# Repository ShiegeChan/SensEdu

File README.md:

<p align="center"><b>Ultrasonic Development Shield for Arduino GIGA R1</b><br>
Designed for education - easy entry into ultrasonic sensing and research</p>

<p align="center">

</p>

<b>
<p align="center">
	<a href="https://github.com/ShiegeChan/SensEdu/releases" target="_blank">Download</a> ·
	<a href="https://sensedu-shield.com/getting-started/" target="_blank">Getting Started</a> ·
	<a href="https://sensedu-shield.com/projects/" target="_blank">Example Projects</a> ·
	<a href="https://sensedu-shield.com" target="_blank">Documentation</a> ·
	<a href="https://sensedu-shield.com/contributing/" target="_blank">Contribution</a>
</p>
</b>

## Features

* **Custom Shield Design** for <a href="https://docs.arduino.cc/hardware/giga-r1-wifi/?queryID=undefined" target="_blank">Arduino GIGA R1 WiFi</a> and mechanically compatible boards (e.g., <a href="https://www.infineon.com/evaluation-board/KIT-A2G-TC375-ARD-SB" target="_blank">AURIX™ TC375 Shieldbuddy</a>). It extends the board with sensors:
  * **4x Infineon MEMS microphones**: capable of operating in ultrasonic range at approx. 20-80 kHz (<a href="https://www.infineon.com/assets/row/public/documents/24/49/infineon-im73a135-datasheet-en.pdf" target="_blank">datasheet</a>).
  * **2x Ultrasonic Transducers**: transmit ultrasonic waves with a center frequency of ~33kHz (<a href="https://www.farnell.com/datasheets/4413630.pdf?_gl=1*1fltz5c*_gcl_au*MTQwMTY3ODgxOC4xNzI2NDc2MDYw" target="_blank">datasheet</a>).
  * **4x Instrumentation Amplifiers**: dual-channel parts providing 8x channels total, four wired to the on-board MEMS microphones and four routed to external pin headers for connecting additional sensors such as surface EMG electrodes (<a href="https://www.analog.com/media/en/technical-documentation/data-sheets/ad8426.pdf" target= "_blank">datasheet</a>).
  * **1x Infineon Barometric Air Pressure Sensor**: provides pressure and temperature measurements; ideal for indoor and outdoor navigation, weather stations, drones, and more (<a href="https://www.infineon.com/assets/row/public/documents/24/49/infineon-dps368-datasheet-en.pdf" target="_blank">datasheet</a>).
  * **1x Sensirion Humidity & Temperature Sensor**: provides relative humidity and temperature readings for environmental compensation and weather monitoring (<a href="https://sensirion.com/media/documents/33FD6951/67EB9032/HT_DS_Datasheet_SHT4x_5.pdf" target="_blank">datasheet</a>).
* **Low-Level SensEdu Library** for Arduino GIGA R1 that serves as a basic abstraction layer for the STM32H747 peripherals and provides default configurations for all sensors. It is implemented at the register level based on <a href="https://www.st.com/resource/en/reference_manual/rm0399-stm32h745755-and-stm32h747757-advanced-armbased-32bit-mcus-stmicroelectronics.pdf" target="_blank">STM32H747 Reference Manual</a> and <a href="https://developer.arm.com/documentation/ddi0403/latest/" target="_blank"> Armv7-M Architecture Reference Manual</a>, ensuring simplicity and expandability. Extensive examples are included to demonstrate library's functionality.
* **Example projects** show how to use SensEdu to achieve your learning goals. See the full implementation for pulsed time-of-flight distance measurements, FMCW ranging, FSK-modulated communication, a weather station, and other projects.
* **MATLAB and Python scripts** enable visualization and post-processing of recorded data transferred via USB or Wi-Fi.

## Preview

## Installation

1. Open the <a href="https://www.arduino.cc/en/software" target="_blank">Arduino IDE</a> and install the **Arduino Mbed OS Giga Boards** package via the Boards Manager.
2. Install the **SensEdu** library via the Library Manager.
3. To run the example projects, download the <a href="https://github.com/ShiegeChan/SensEdu/releases" target="_blank">latest release</a> and extract the **projects** folder anywhere on your system.

> A more complete walkthrough is available in the <a href="https://sensedu-shield.com/getting-started/" target="_blank">Getting Started</a> guide on the documentation website.

## Starting a Project

To get started, you can explore the hardware interface by following the examples provided in the SensEdu library (`Arduino\libraries\SensEdu\examples\`). A detailed description of all functions can be found in the <a href="https://sensedu-shield.com/library/" target="_blank">Documentation</a> under the "SensEdu Library" section.

In the `projects/` directory, you will find several complete projects designed for this board, including:
* **Ultrasonic Pulse-Echo Ranging**
* **Ultrasonic 3D Tracking**
* **Ultrasonic Chirp Generation**
* **Ultrasonic FMCW Ranging**
* **Ultrasonic FSK Communication Link**
* **Audio Recorder**
* **EMG BioInputs** - *coming soon*
* **Weather Station**

Detailed overview for each project is available in the "Projects" section of the <a href="https://sensedu-shield.com/projects/" target="_blank">Documentation</a>.

## Support

If you would like to contribute, please open a pull request!
Suggest improvements or check out already opened <a href="https://github.com/ShiegeChan/SensEdu/issues" target="_blank">issues</a> to help fix bugs or add new features.

## Acknowledgments

SensEdu was made possible thanks to these tools and libraries:

* [Arduino], [Arduino IDE 2.x] and the [Arduino Mbed OS Giga Core]
* [STM32H747 Documentation] and [STM32CubeMX]
* [CMSIS-DSP]
* [XENSIV™ Digital Pressure Sensor Arduino Library] and [Sensirion SHT4x Arduino Library]
* [KiCad]
* [MATLAB] and [Python]
* [Manim Community]
* [Jekyll] and [Just the Docs] template

## License

* [**GPL-3.0 license**](https://github.com/ShiegeChan/SensEdu/blob/main/LICENSE)

[Arduino IDE 2.x]: https://github.com/arduino/arduino-ide
[Arduino]: https://www.arduino.cc/
[Arduino Mbed OS Giga Core]: https://github.com/arduino/ArduinoCore-mbed
[XENSIV™ Digital Pressure Sensor Arduino Library]: https://github.com/Infineon/arduino-xensiv-dps3xx
[Sensirion SHT4x Arduino Library]: https://github.com/Sensirion/arduino-i2c-sht4x
[STM32H747 Documentation]: https://www.st.com/en/microcontrollers-microprocessors/stm32h747-757/documentation.html
[STM32CubeMX]: https://www.st.com/en/development-tools/stm32cubemx.html
[CMSIS-DSP]: https://github.com/ARM-software/CMSIS-DSP
[MATLAB]: https://www.mathworks.com/products/matlab.html
[Python]: https://www.python.org/
[Manim Community]: https://docs.manim.community/en/stable/index.html
[Jekyll]: https://jekyllrb.com/
[Just the Docs]: https://just-the-docs.com/
[KiCad]: https://www.kicad.org/

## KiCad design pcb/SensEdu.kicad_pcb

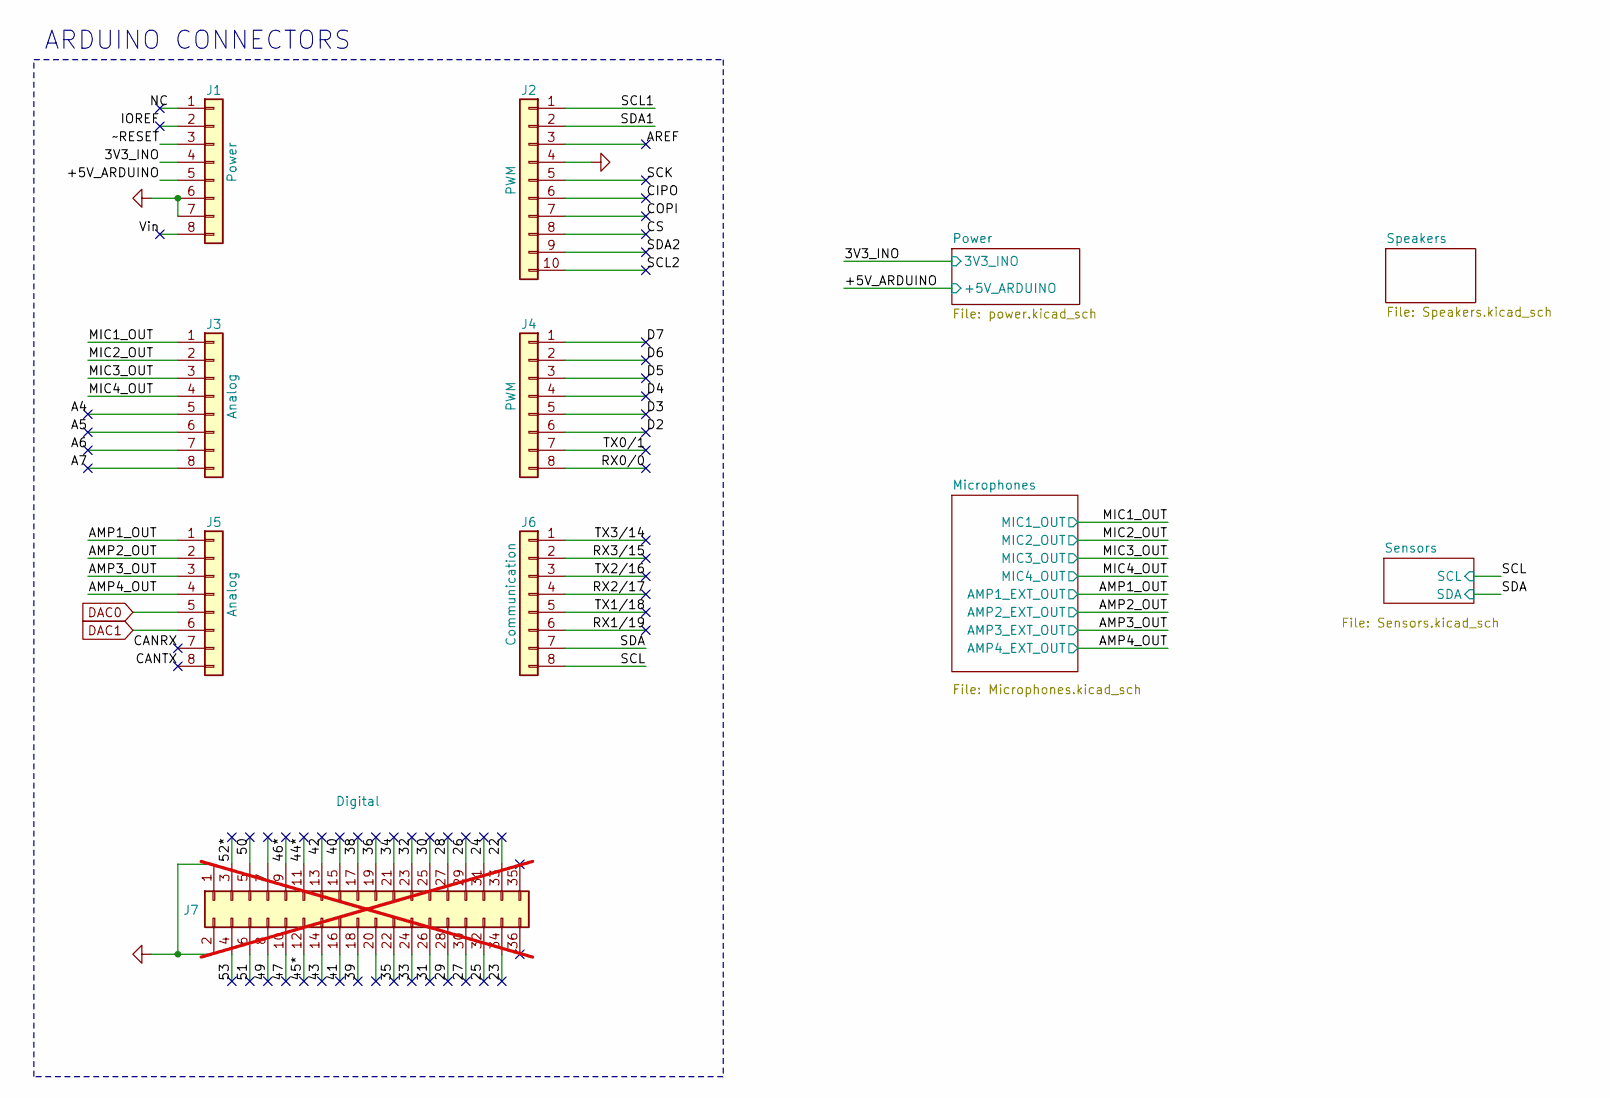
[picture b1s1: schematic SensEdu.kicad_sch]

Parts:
J1: Power; PinSocket_1x08_P2.54mm_Vertical
J2: PWM; PinSocket_1x10_P2.54mm_Vertical
J3, J5: Analog; PinSocket_1x08_P2.54mm_Vertical
J4: PWM; PinSocket_1x08_P2.54mm_Vertical
J6: Communication; PinSocket_1x08_P2.54mm_Vertical
J7: Digital; PinSocket_2x18_P2.54mm_Vertical; not fitted

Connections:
/3V3_INO: J1.4; also elsewhere on the board
/22: J7.33
/23: J7.34
/24: J7.31
/25: J7.32
/26: J7.29
/27: J7.30
/28: J7.27
/29: J7.28
/30: J7.25
/31: J7.26
/32: J7.23
/33: J7.24
/34: J7.21
/35: J7.22
/36: J7.19
/38: J7.17
/39: J7.18
/40: J7.15
/41: J7.16
/42: J7.13
/43: J7.14
/44*: J7.11
/45*: J7.12
/46*: J7.9
/47: J7.10
/49: J7.8
/50: J7.5
/51: J7.6
/52*: J7.3
/53: J7.4
/+5V_ARDUINO: J1.5; also elsewhere on the board
/A4: J3.5
/A5: J3.6
/A6: J3.7
/A7: J3.8
/AMP1_OUT: J5.1; also elsewhere on the board
/AMP2_OUT: J5.2; also elsewhere on the board
/AMP3_OUT: J5.3; also elsewhere on the board
/AMP4_OUT: J5.4; also elsewhere on the board
/AREF: J2.3
/CANRX: J5.7
/CANTX: J5.8
/CIPO: J2.6
/COPI: J2.7
/CS: J2.8
/D2: J4.6
/D3: J4.5
/D4: J4.4
/D5: J4.3
/D6: J4.2
/D7: J4.1
/IOREF: J1.2
/MIC1_OUT: J3.1; also elsewhere on the board
/MIC2_OUT: J3.2; also elsewhere on the board
/MIC3_OUT: J3.3; also elsewhere on the board
/MIC4_OUT: J3.4; also elsewhere on the board
/NC: J1.1
/RX0/0: J4.8
/RX1/19: J6.6
/RX2/17: J6.4
/RX3/15: J6.2
/SCK: J2.5
/SCL: J6.8; also elsewhere on the board
/SCL1: J2.1
/SCL2: J2.10
/SDA: J6.7; also elsewhere on the board
/SDA1: J2.2
/SDA2: J2.9
/TX0/1: J4.7
/TX1/18: J6.5
/TX2/16: J6.3
/TX3/14: J6.1
/Vin: J1.8
/~RESET: J1.3
DAC0: J5.5; also elsewhere on the board
DAC1: J5.6; also elsewhere on the board
GND: J1.6, J1.7, J2.4, J7.1, J7.2; also elsewhere on the board

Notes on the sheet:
ARDUINO CONNECTORS

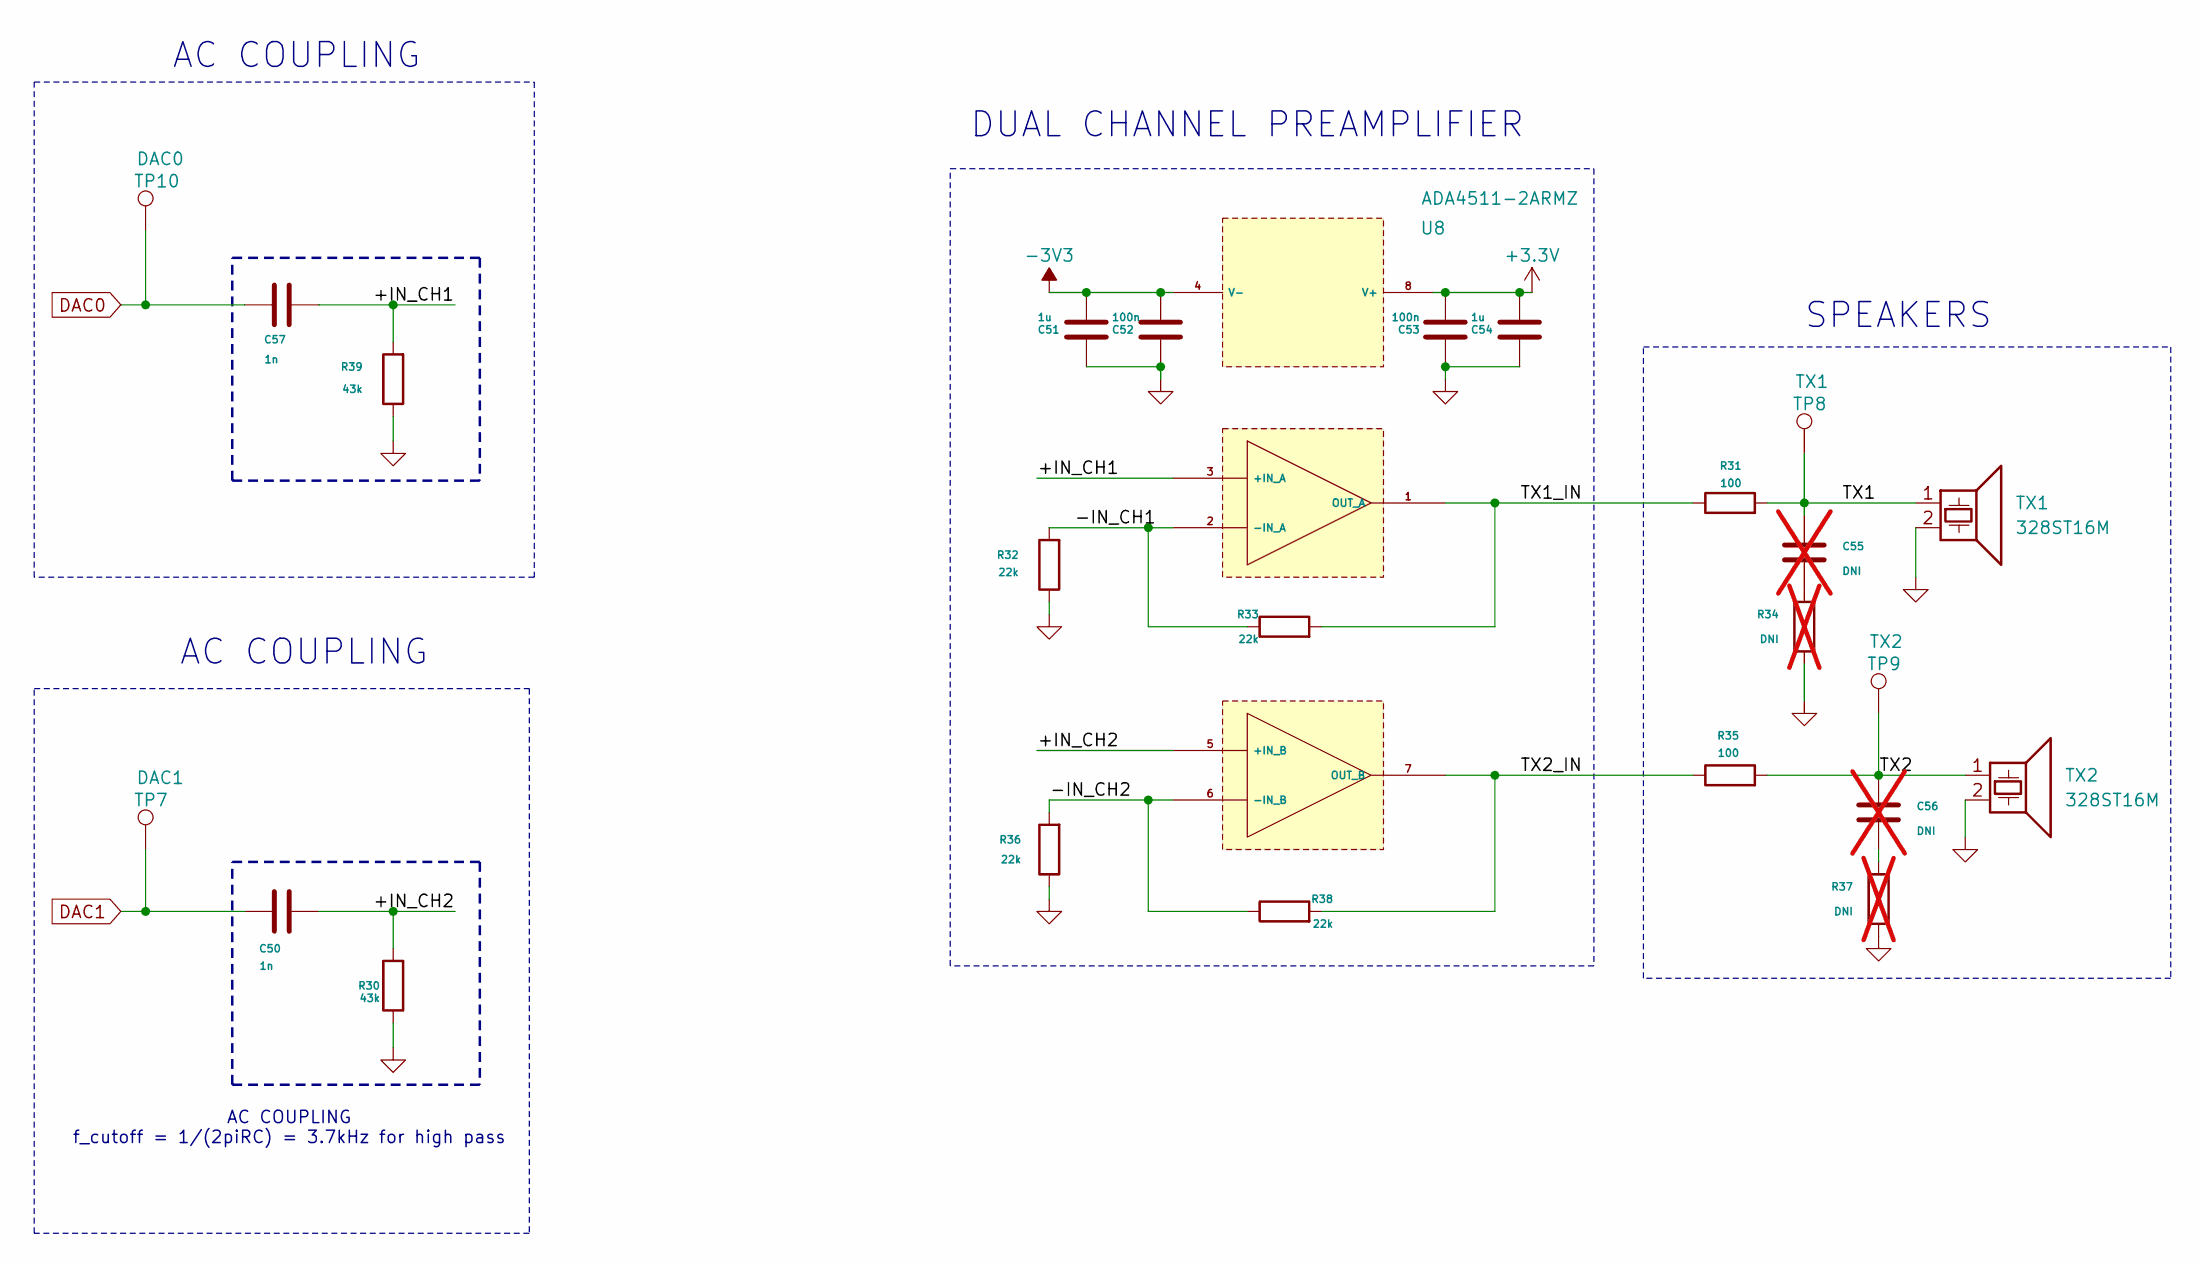
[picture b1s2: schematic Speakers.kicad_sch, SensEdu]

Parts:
C50, C57: 1n; C_0603_1608Metric
C51, C54: 1u; C_0603_1608Metric
C52, C53: 100n; C_0603_1608Metric
C55, C56: DNI; C_0603_1608Metric; not fitted
R30, R39: 43k; R_0603_1608Metric
R31, R35: 100; R_0603_1608Metric
R32, R33, R36, R38: 22k; R_0603_1608Metric
R34, R37: DNI; R_0603_1608Metric; not fitted
TP7: DAC1; TestPoint_THTPad_D2.0mm_Drill1.0mm
TP8: TX1; TestPoint_THTPad_D2.0mm_Drill1.0mm
TP9: TX2; TestPoint_THTPad_D2.0mm_Drill1.0mm
TP10: DAC0; TestPoint_THTPad_D2.0mm_Drill1.0mm
TX1, TX2: 328ST16M; 328ST16M_Speaker
U8: ADA4511-2ARMZ; SOP65P490X110-8N; Manufacturer_Part_Number ADA4511-2ARMZ

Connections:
+3.3V: C53.2, C54.1, U8.8 (V+); also elsewhere on the board
-3V3: C51.1, C52.1, U8.4 (V-); also elsewhere on the board
/Speakers/+IN_CH1: C57.2, R39.2, U8.3 (+IN_A)
/Speakers/+IN_CH2: C50.2, R30.2, U8.5 (+IN_B)
/Speakers/-IN_CH1: R32.2, R33.1, U8.2 (-IN_A)
/Speakers/-IN_CH2: R36.2, R38.1, U8.6 (-IN_B)
/Speakers/TX1: C55.1, R31.2, TP8.1, TX1.1
/Speakers/TX1_IN: R31.1, R33.2, U8.1 (OUT_A)
/Speakers/TX2: C56.1, R35.2, TP9.1, TX2.1
/Speakers/TX2_IN: R35.1, R38.2, U8.7 (OUT_B)
DAC0: C57.1, TP10.1; also elsewhere on the board
DAC1: C50.1, TP7.1; also elsewhere on the board
GND: C51.2, C52.2, C53.1, C54.2, R30.1, R32.1, R34.1, R36.1, R37.1, R39.1, TX1.2, TX2.2; also elsewhere on the board
unnamed: C55.2, R34.2
unnamed: C56.2, R37.2

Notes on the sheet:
AC COUPLING f_cutoff = 1/(2piRC) = 3.7kHz for high pass
AC COUPLING
SPEAKERS
DUAL CHANNEL PREAMPLIFIER
AC COUPLING

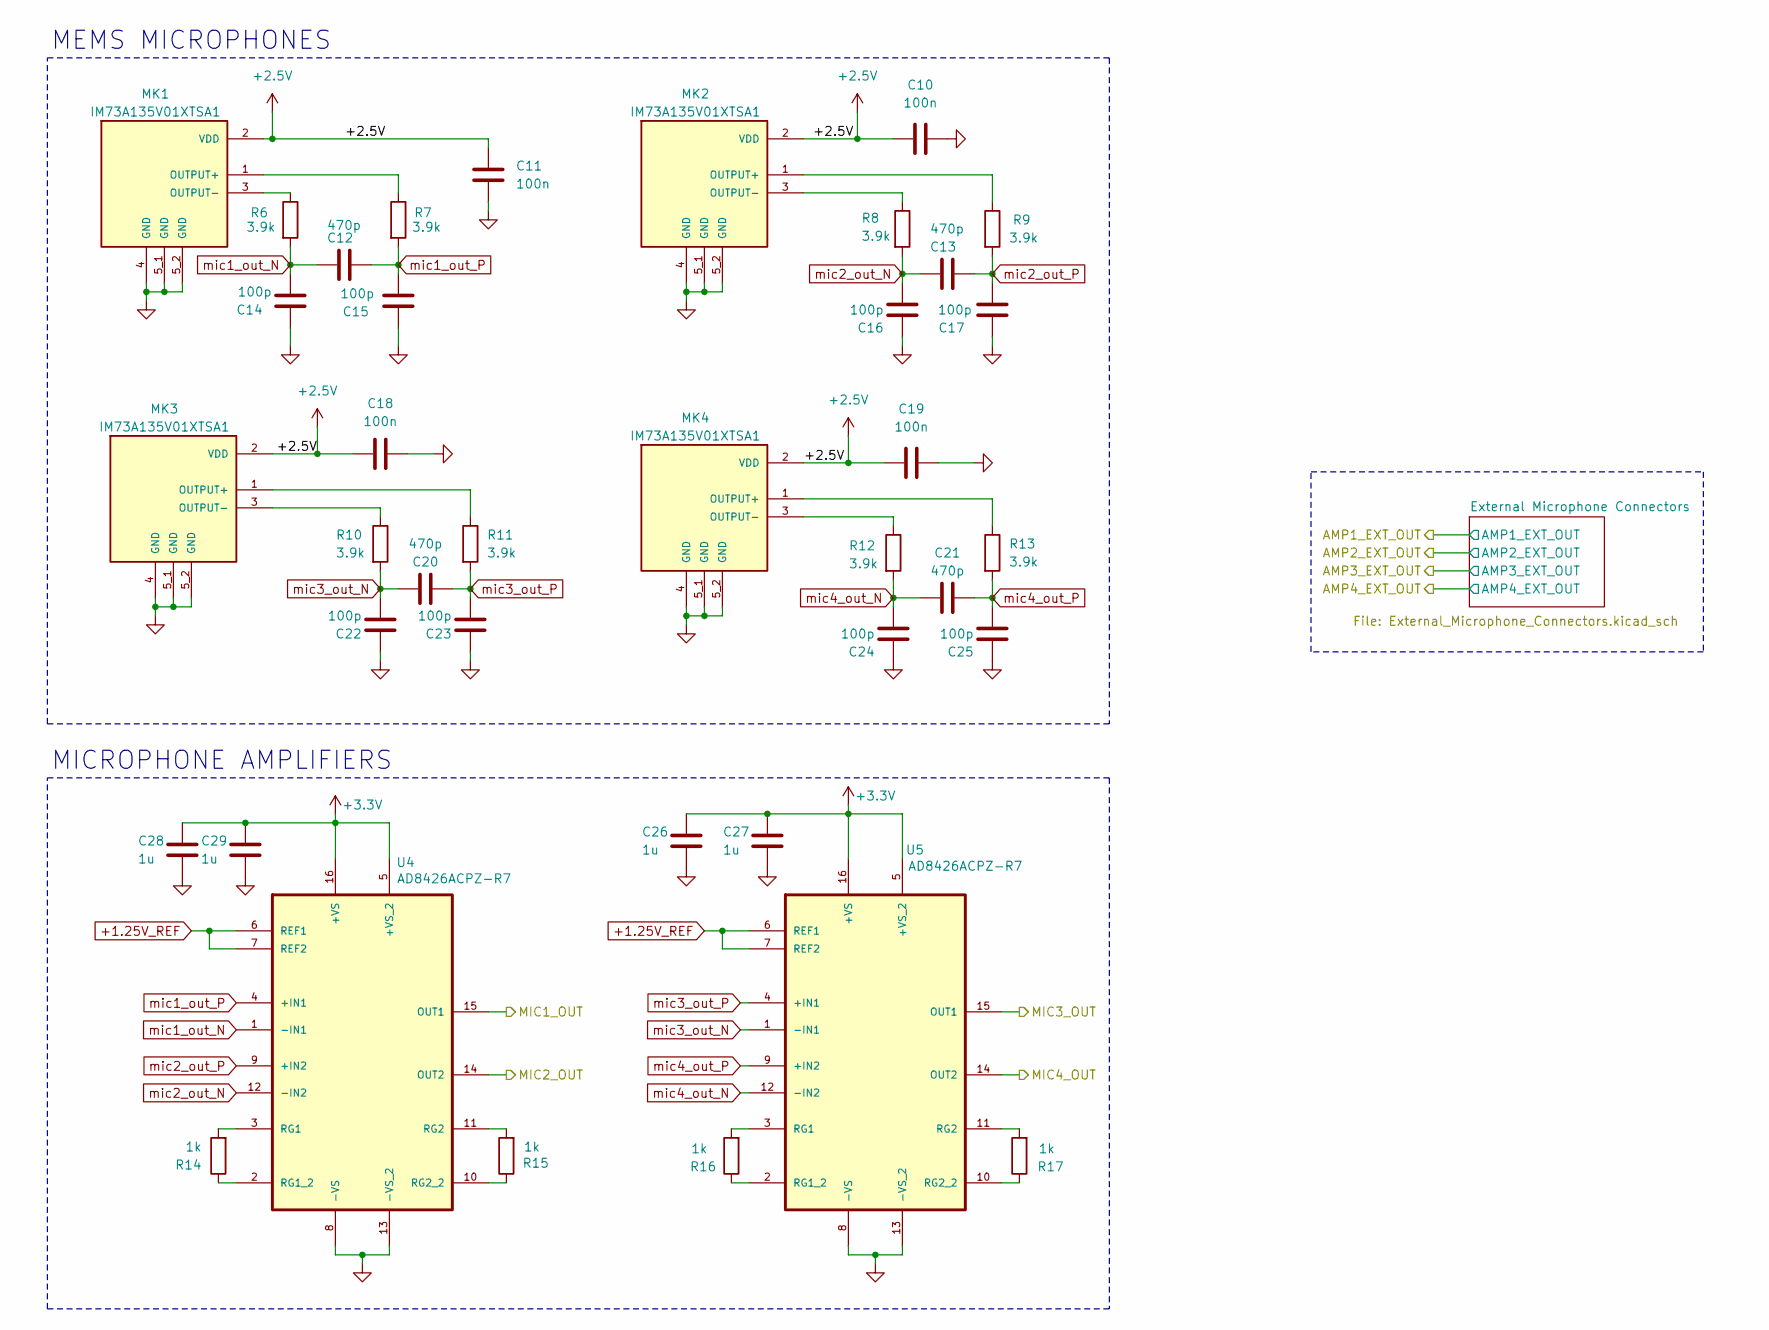
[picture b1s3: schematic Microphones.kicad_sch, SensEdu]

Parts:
C10, C11, C18, C19: 100n; C_0603_1608Metric
C12, C13, C20, C21: 470p; C_0603_1608Metric
C14, C15, C16, C17, C22, C23, C24, C25: 100p; C_0603_1608Metric
C26, C27, C28, C29: 1u; C_0603_1608Metric
MK1, MK2, MK3, MK4: IM73A135V01XTSA1; MIC_IM73A135V01XTSA1; PARTREV V1.20
R6, R7, R8, R9, R10, R11, R12, R13: 3.9k; R_0603_1608Metric
R14, R15, R16, R17: 1k; R_0603_1608Metric
U4, U5: AD8426ACPZ-R7; QFN65P400X400X100-16N; MPN AD8426ACPZ-R7

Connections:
+1.25V_REF: U4.6 (REF1), U4.7 (REF2), U5.6 (REF1), U5.7 (REF2); also elsewhere on the board
+2.5V: C10.1, C11.1, C18.1, C19.1, MK1.2 (VDD), MK2.2 (VDD), MK3.2 (VDD), MK4.2 (VDD); also elsewhere on the board
+3.3V: C26.1, C27.1, C28.1, C29.1, U4.5 (+VS_2), U4.16 (+VS), U5.5 (+VS_2), U5.16 (+VS); also elsewhere on the board
/MIC1_OUT: U4.15 (OUT1); also elsewhere on the board
/MIC2_OUT: U4.14 (OUT2); also elsewhere on the board
/MIC3_OUT: U5.15 (OUT1); also elsewhere on the board
/MIC4_OUT: U5.14 (OUT2); also elsewhere on the board
GND: C10.2, C11.2, C14.1, C15.1, C16.1, C17.1, C18.2, C19.2, C22.1, C23.1, C24.1, C25.1, C26.2, C27.2, C28.2, C29.2, MK1.4 (GND), MK1.5_1 (GND), MK1.5_2 (GND), MK2.4 (GND), MK2.5_1 (GND), MK2.5_2 (GND), MK3.4 (GND), MK3.5_1 (GND), MK3.5_2 (GND), MK4.4 (GND), MK4.5_1 (GND), MK4.5_2 (GND), U4.8 (-VS), U4.13 (-VS_2), U5.8 (-VS), U5.13 (-VS_2); also elsewhere on the board
unnamed: MK1.1 (OUTPUT+), R7.1
unnamed: MK1.3 (OUTPUT-), R6.1
unnamed: MK2.1 (OUTPUT+), R9.1
unnamed: MK2.3 (OUTPUT-), R8.1
unnamed: MK3.1 (OUTPUT+), R11.1
unnamed: MK3.3 (OUTPUT-), R10.1
unnamed: MK4.1 (OUTPUT+), R13.1
unnamed: MK4.3 (OUTPUT-), R12.1
unnamed: R14.2, U4.3 (RG1)
unnamed: R14.1, U4.2 (RG1_2)
unnamed: R15.2, U4.11 (RG2)
unnamed: R15.1, U4.10 (RG2_2)
unnamed: R16.2, U5.3 (RG1)
unnamed: R16.1, U5.2 (RG1_2)
unnamed: R17.2, U5.11 (RG2)
unnamed: R17.1, U5.10 (RG2_2)
mic1_out_N: C12.2, C14.2, R6.2, U4.1 (-IN1)
mic1_out_P: C12.1, C15.2, R7.2, U4.4 (+IN1)
mic2_out_N: C13.2, C16.2, R8.2, U4.12 (-IN2)
mic2_out_P: C13.1, C17.2, R9.2, U4.9 (+IN2)
mic3_out_N: C20.2, C22.2, R10.2, U5.1 (-IN1)
mic3_out_P: C20.1, C23.2, R11.2, U5.4 (+IN1)
mic4_out_N: C21.2, C24.2, R12.2, U5.12 (-IN2)
mic4_out_P: C21.1, C25.2, R13.2, U5.9 (+IN2)

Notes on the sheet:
MEMS MICROPHONES
MICROPHONE AMPLIFIERS

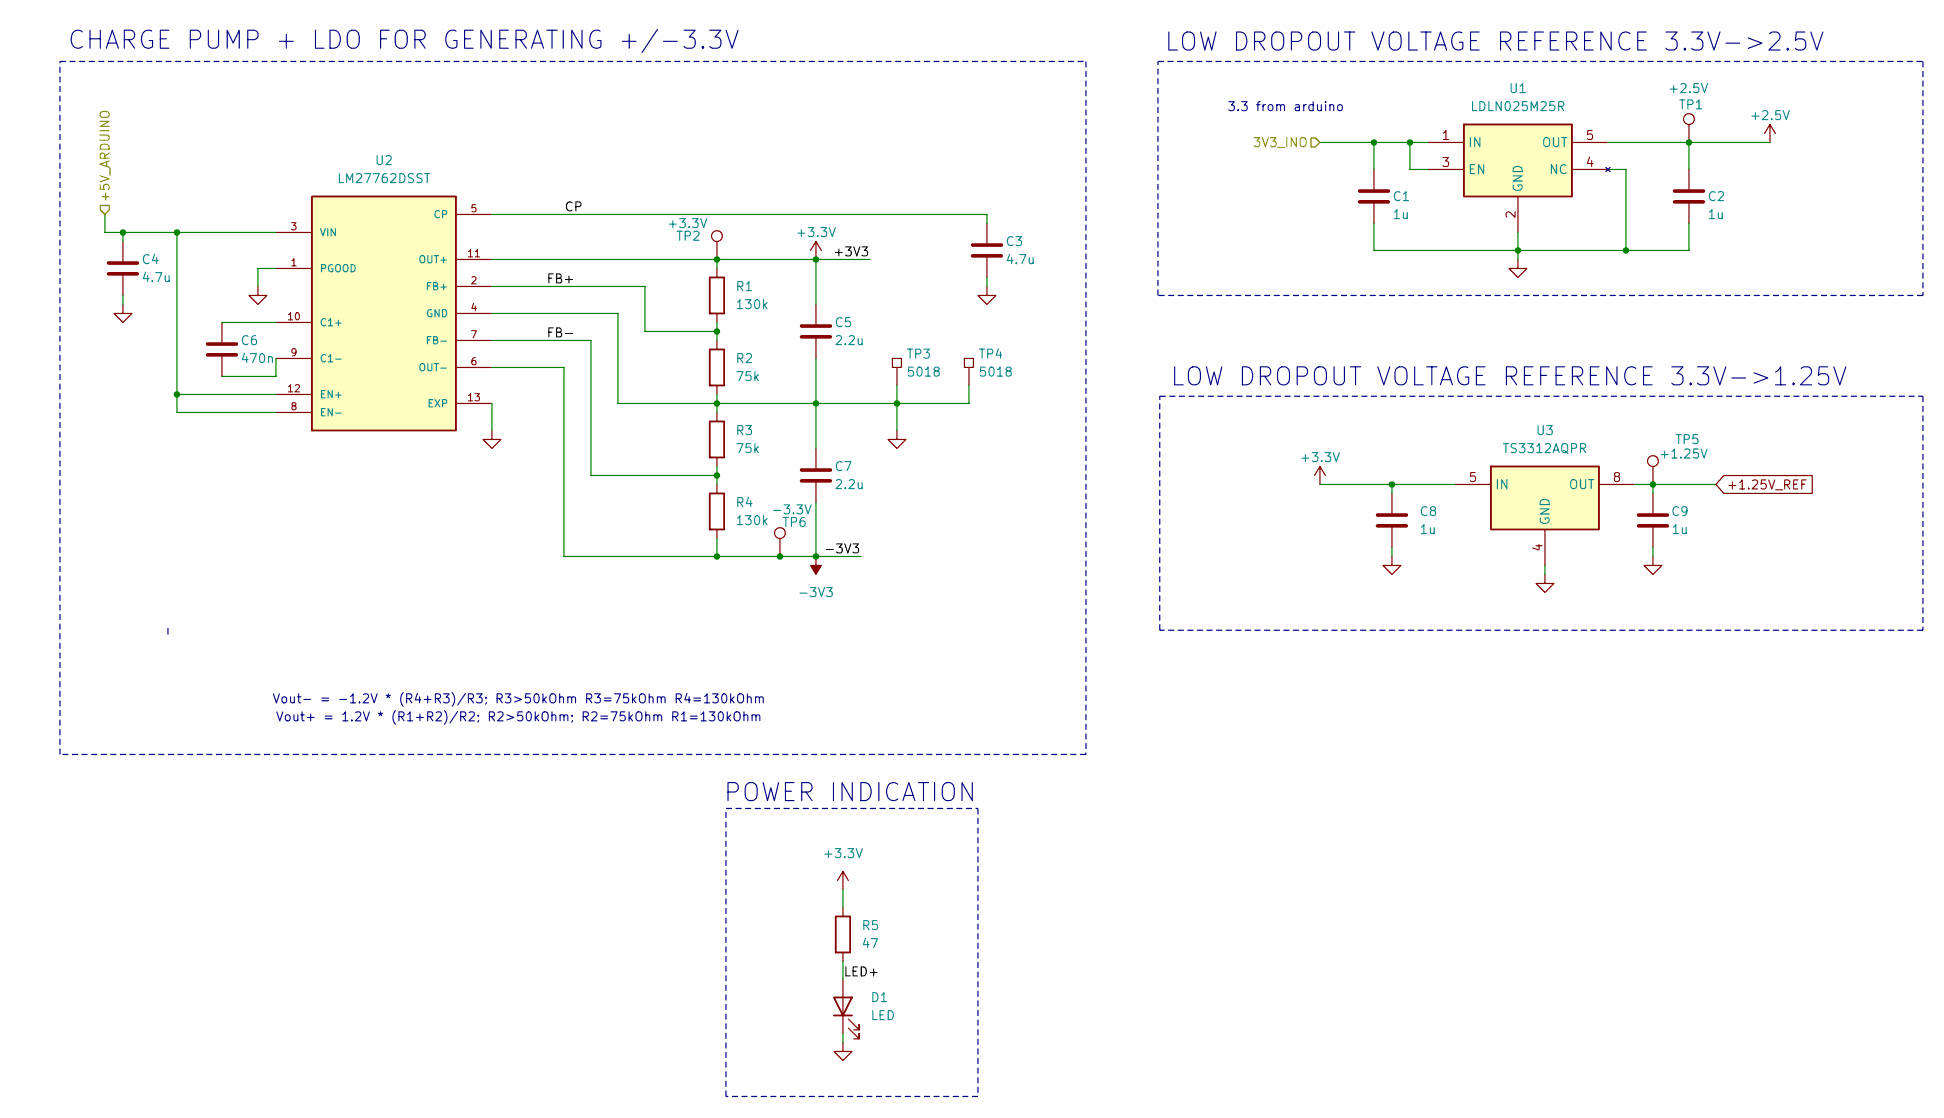
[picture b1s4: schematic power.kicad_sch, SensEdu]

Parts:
C1, C2, C8, C9: 1u; C_0603_1608Metric
C3, C4: 4.7u; C_0805_2012Metric
C5, C7: 2.2u; C_0805_2012Metric
C6: 470n; C_0603_1608Metric
D1: LED; LED_0805_2012Metric
R1, R4: 130k; R_0603_1608Metric
R2, R3: 75k; R_0603_1608Metric
R5: 47; R_0603_1608Metric
TP1: +2.5V; TestPoint_THTPad_D2.0mm_Drill1.0mm
TP2: +3.3V; TestPoint_THTPad_D2.0mm_Drill1.0mm
TP3, TP4: 5018; Manufacturer_Part_Number 5018; Mouser Part Number 534-5018
TP5: +1.25V; TestPoint_THTPad_D2.0mm_Drill1.0mm
TP6: -3.3V; TestPoint_THTPad_D2.0mm_Drill1.0mm
U1: LDLN025M25R; SOT95P280X145-5N; Manufacturer_Part_Number LDLN025M25R; Mouser Part Number 511-LDLN025M25R
U2: LM27762DSST; IC_LM27762DSST; PARTREV B
U3: TS3312AQPR; Manufacturer_Part_Number TS3312AQPR; Mouser Part Number 511-TS3312AQPR

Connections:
+1.25V_REF: C9.2, TP5.1, U3.8 (OUT); also elsewhere on the board
+2.5V: C2.1, TP1.1, U1.5 (OUT); also elsewhere on the board
+3.3V: C5.1, C8.1, R1.1, R5.1, TP2.1, U2.11 (OUT+), U3.5 (IN); also elsewhere on the board
-3V3: C7.2, R4.2, TP6.1, U2.6 (OUT-); also elsewhere on the board
/3V3_INO: C1.1, U1.1 (IN), U1.3 (EN); also elsewhere on the board
/+5V_ARDUINO: C4.1, U2.3 (VIN), U2.8 (EN-), U2.12 (EN+); also elsewhere on the board
/Power/CP: C3.1, U2.5 (CP)
/Power/FB+: R1.2, R2.1, U2.2 (FB+)
/Power/FB-: R3.2, R4.1, U2.7 (FB-)
/Power/LED+: D1.2 (A), R5.2
GND: C1.2, C2.2, C3.2, C4.2, C5.2, C7.1, C8.2, C9.1, D1.1 (K), R2.2, R3.1, TP3.1, TP4.1, U1.2 (GND), U1.4 (NC), U2.1 (PGOOD), U2.4 (GND), U2.13 (EXP), U3.4 (GND); also elsewhere on the board
unnamed: C6.1, U2.10 (C1+)
unnamed: C6.2, U2.9 (C1-)

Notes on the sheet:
CHARGE PUMP + LDO FOR GENERATING +/-3.3V
Vout- = -1.2V * (R4+R3)/R3; R3>50kOhm R3=75kOhm R4=130kOhm
POWER INDICATION
LOW DROPOUT VOLTAGE REFERENCE 3.3V->1.25V
Vout+ = 1.2V * (R1+R2)/R2; R2>50kOhm; R2=75kOhm R1=130kOhm
LOW DROPOUT VOLTAGE REFERENCE 3.3V->2.5V
3.3 from arduino

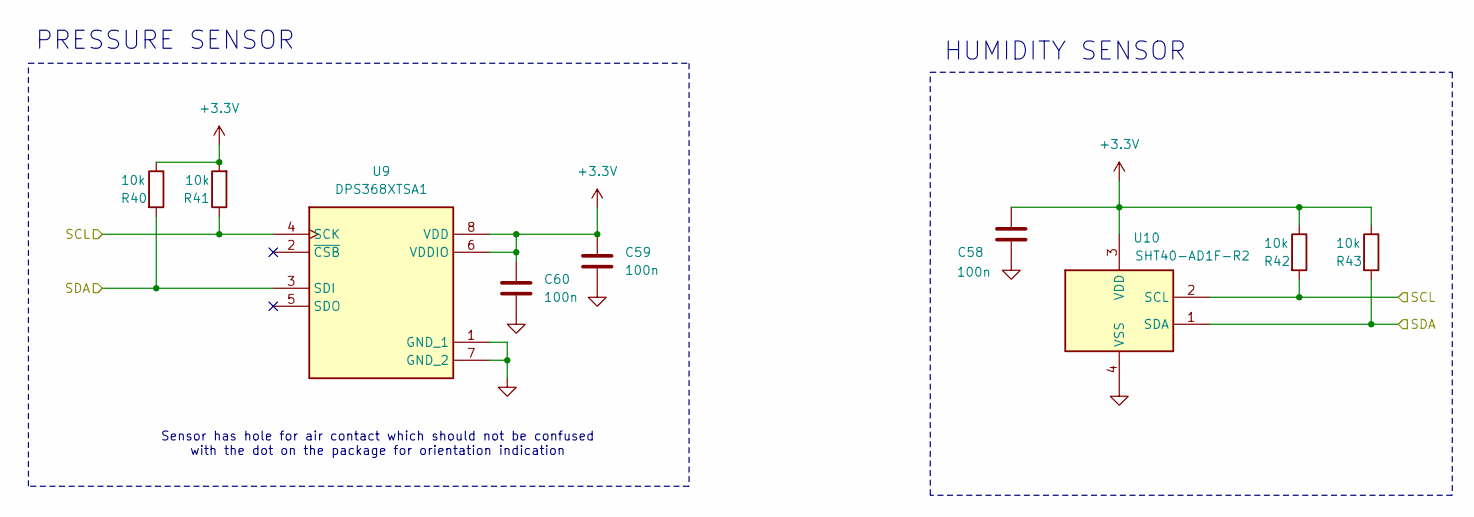
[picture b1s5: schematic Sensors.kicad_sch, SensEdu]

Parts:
C58, C59, C60: 100n; C_0603_1608Metric
R40, R41, R42, R43: 10k; R_0603_1608Metric
U9: DPS368XTSA1; Mouser Part Number 726-DPS368XTSA1
U10: SHT40-AD1F-R2; SHT40AD1FR2; Manufacturer_Part_Number SHT40-AD1F-R2; Mouser Part Number 403-SHT40-AD1F-R2

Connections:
+3.3V: C58.2, C59.1, C60.1, R40.1, R41.2, R42.1, R43.1, U9.6 (VDDIO), U9.8 (VDD), U10.3 (VDD); also elsewhere on the board
/SCL: R41.1, R42.2, U9.4 (SCK), U10.2 (SCL); also elsewhere on the board
/SDA: R40.2, R43.2, U9.3 (SDI), U10.1 (SDA); also elsewhere on the board
GND: C58.1, C59.2, C60.2, U9.1 (GND_1), U9.7 (GND_2), U10.4 (VSS); also elsewhere on the board

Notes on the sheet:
Sensor has hole for air contact which should not be confused with the dot on the package for orientation indication
PRESSURE SENSOR
HUMIDITY SENSOR

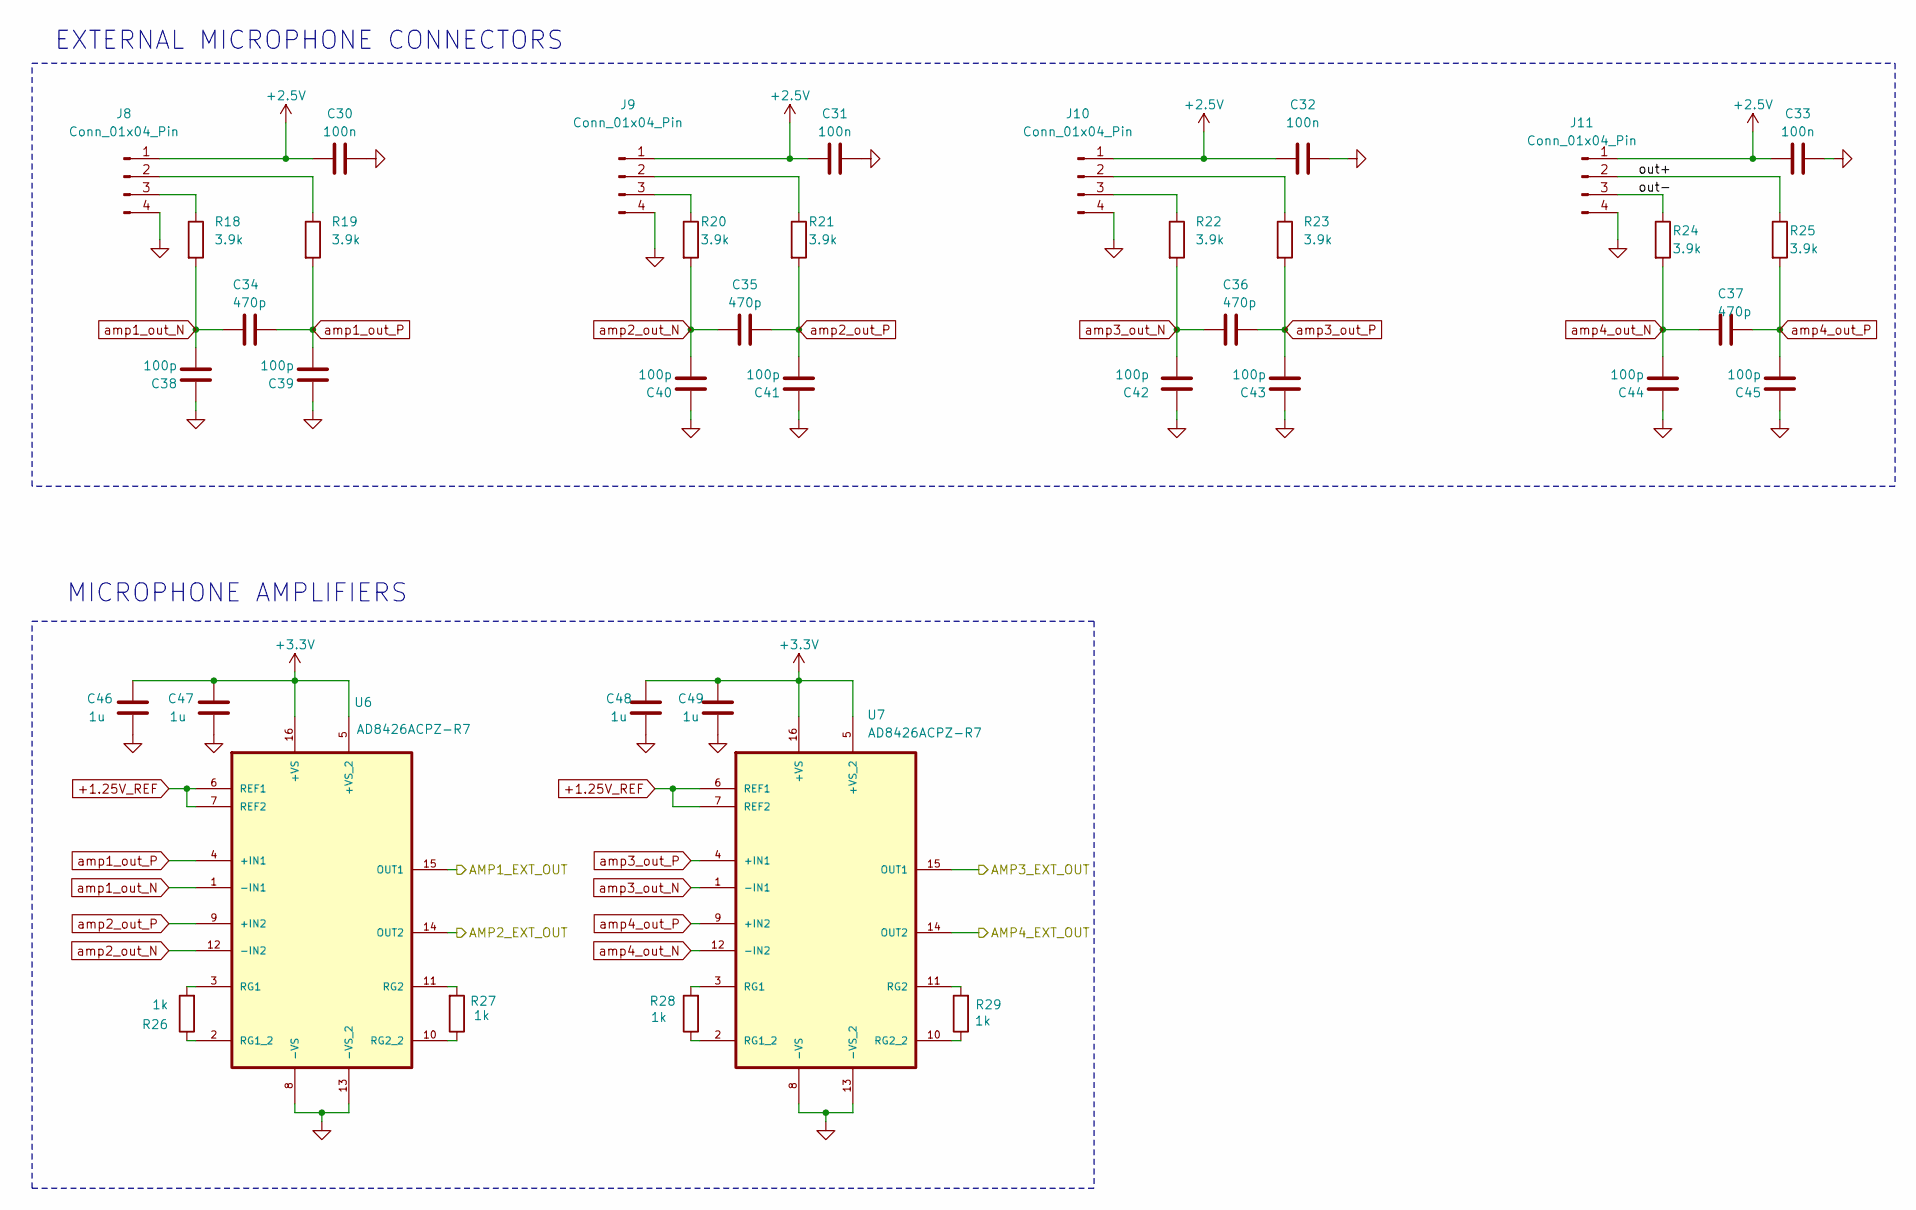
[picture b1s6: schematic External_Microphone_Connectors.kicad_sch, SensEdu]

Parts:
C30, C31, C32, C33: 100n; C_0603_1608Metric
C34, C35, C36, C37: 470p; C_0603_1608Metric
C38, C39, C40, C41, C42, C43, C44, C45: 100p; C_0603_1608Metric
C46, C47, C48, C49: 1u; C_0603_1608Metric
J8, J9, J10, J11: Conn_01x04_Pin; PinSocket_1x04_P2.54mm_Vertical
R18, R19, R20, R21, R22, R23, R24, R25: 3.9k; R_0603_1608Metric
R26, R27, R28, R29: 1k; R_0603_1608Metric
U6, U7: AD8426ACPZ-R7; QFN65P400X400X100-16N; MPN AD8426ACPZ-R7

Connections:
+1.25V_REF: U6.6 (REF1), U6.7 (REF2), U7.6 (REF1), U7.7 (REF2); also elsewhere on the board
+2.5V: C30.1, C31.1, C32.1, C33.1, J8.1, J9.1, J10.1, J11.1; also elsewhere on the board
+3.3V: C46.1, C47.1, C48.1, C49.1, U6.5 (+VS_2), U6.16 (+VS), U7.5 (+VS_2), U7.16 (+VS); also elsewhere on the board
/AMP1_OUT: U6.15 (OUT1); also elsewhere on the board
/AMP2_OUT: U6.14 (OUT2); also elsewhere on the board
/AMP3_OUT: U7.15 (OUT1); also elsewhere on the board
/AMP4_OUT: U7.14 (OUT2); also elsewhere on the board
/Microphones/External Microphone Connectors/out+: J11.2, R25.1
/Microphones/External Microphone Connectors/out-: J11.3, R24.1
GND: C30.2, C31.2, C32.2, C33.2, C38.1, C39.1, C40.1, C41.1, C42.1, C43.1, C44.1, C45.1, C46.2, C47.2, C48.2, C49.2, J8.4, J9.4, J10.4, J11.4, U6.8 (-VS), U6.13 (-VS_2), U7.8 (-VS), U7.13 (-VS_2); also elsewhere on the board
unnamed: J8.2, R19.1
unnamed: J8.3, R18.1
unnamed: J9.2, R21.1
unnamed: J9.3, R20.1
unnamed: J10.2, R23.1
unnamed: J10.3, R22.1
unnamed: R26.2, U6.3 (RG1)
unnamed: R26.1, U6.2 (RG1_2)
unnamed: R27.2, U6.11 (RG2)
unnamed: R27.1, U6.10 (RG2_2)
unnamed: R28.2, U7.3 (RG1)
unnamed: R28.1, U7.2 (RG1_2)
unnamed: R29.2, U7.11 (RG2)
unnamed: R29.1, U7.10 (RG2_2)
amp1_out_N: C34.2, C38.2, R18.2, U6.1 (-IN1)
amp1_out_P: C34.1, C39.2, R19.2, U6.4 (+IN1)
amp2_out_N: C35.2, C40.2, R20.2, U6.12 (-IN2)
amp2_out_P: C35.1, C41.2, R21.2, U6.9 (+IN2)
amp3_out_N: C36.2, C42.2, R22.2, U7.1 (-IN1)
amp3_out_P: C36.1, C43.2, R23.2, U7.4 (+IN1)
amp4_out_N: C37.2, C44.2, R24.2, U7.12 (-IN2)
amp4_out_P: C37.1, C45.2, R25.2, U7.9 (+IN2)

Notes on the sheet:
MICROPHONE AMPLIFIERS
EXTERNAL MICROPHONE CONNECTORS
